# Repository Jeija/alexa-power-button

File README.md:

# Alexa / Dash Button = PC power button
If you like to hide your desktop computer case so that it's not in the way, you probably know that it can be quite annoying to have to press the power button in an uncomfortable location every time you want to turn on your PC. `alexa-power-button` solves this by enabling you to use both voice commands for Amazon's digital assistant "Alexa" and/or an Amazon Dash Button to start your computer.

## Hardware
`alexa-power-button` doesn't use Wake on LAN so that you can save energy by turning off all of the attached network equipment apart from a single WiFi router in your home. Instead, the only additional active device is a small ESP32-based PCB inside the computer case that can be programmed and powered using the mainboard's internal USB connectors. Most mainboards can charge phones and other USB devices while the PC is turned off, and this current is more than enough to power the ESP32. The PCB contains n-channel MOSFETs that can be used to pull the power / reset button data line low. This assumes that the power / reset button input of the mainboard consists of an active-low input pin with a positive bias voltage. This pin should then be connected to the MOSFET's drain.

The KiCad design files (schematic, PCB layout) are provided in `hardware`.

## Dash Button Setup
* Use the Amazon App to configure the dash button
* In the last step, don't select which of the products in the list to order
* Press the dash button and use wireshark or similar tools to get the button's MAC address
* In the `firmware` directory: Execute `idf.py menuconfig` and enter the Dash Button's MAC Address in `Alexa Power Button --> Dash Button MAC Address` (including colons)

After flashing the firmware, the ESP32 will capture all WiFi traffic and check if source or destination address of the IEEE 802.11 header match the provided Dash Button MAC address.

## Alexa Skill + AWS MQTT / Lambda Setup
* Follow some of the [commonly available](https://www.hackster.io/darian-johnson/diy-smart-lamp-controlled-by-toggle-switch-and-alexa-7de243) [tutorials](https://developer.amazon.com/blogs/post/Tx4WG410EHXIYQ/five-steps-before-developing-a-smart-home-skill) on how to create an Alexa Skill, set up a Lambda function and set up AWS IoT for MQTT
* Make sure to select Payload Version `v2 (legacy)` when creating the Alexa Skill
* Upload the Lambda function. If you have the AWS CLI set up, you can use the Makefile provided in `aws` to upload and test the code.
* Add `THING_ENDPOINT` (AWS IoT HTTPS REST API endpoint host, see the thing's Interact page in AWS IoT) and `MQTT_BASE_TOPIC` (prefix for MQTT topic, e.g. `myhome/mypc`) as environment variables for the Lambda function
* Get your device private key and device certificate from AWS IoT and copy them to `firmware/main/certs` as `private.pem.key` and `certificate.pem.crt` respectively. See [esp-idf's AWS IoT documentation](https://github.com/espressif/esp-idf/tree/master/examples/protocols/aws_iot) for details.
* Confgiure the firmware: Run `idf.py menuconfig` in `firmware` and add your WiFi SSID and password in `Alexa Power Button`. Configure your (arbitrary but unique) AWS IoT Client ID and add the same MQTT base topic as specified in your Lambda function environment variable. Under `Component Config --> Amazon Web Services IoT Platform`, add your AWS IoT HTTPS REST API endpoint host, see the thing's Interact page on AWS IoT.
* Flash the firmware. If errors occur while connecting to AWS IoT, see [the documentation in esp-idf](https://github.com/espressif/esp-idf/tree/master/examples/protocols/aws_iot) for some common problems.

## Flash the firmware
* Use `idf.py menuconfig` in `firmware` to configure your python executable, serial port and flasher baud rate
* `alexa-power-button` uses the usual esp-idf CMake build system and workflow. Run `idf.py all` and `idf.py flash` in `firmware` in order to compile and flash the firmware to your ESP32 board.

## Attribution
* ESP32 schematic symbol and footprint: [adamjvr's ESP32-kiCAD-Footprints
](https://github.com/adamjvr/ESP32-kiCAD-Footprints)
* Alexa Skill Lambda function validation (`aws/validation.js`): [Amazon's alexa-smarthome-validation](https://github.com/alexa/alexa-smarthome-validation)
* ESP32 code: Roughly based on esp-idf's [AWS IoT Subscribe/Publish Example](https://github.com/espressif/esp-idf/tree/master/examples/protocols/aws_iot/subscribe_publish)

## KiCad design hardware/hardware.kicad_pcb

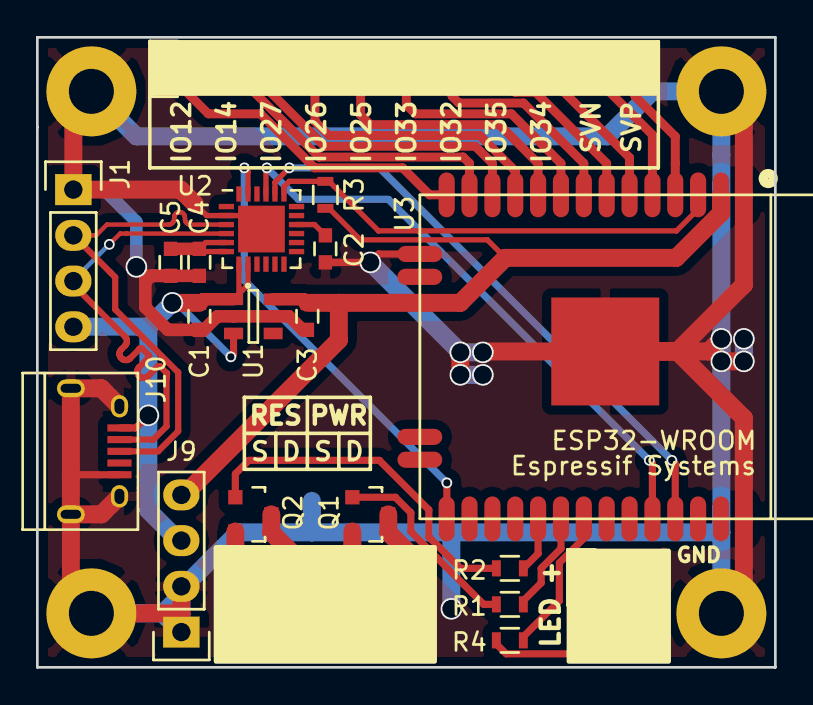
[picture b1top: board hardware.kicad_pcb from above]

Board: 2 copper layers, 41.0 x 35.0 mm, 24 parts (0 on the bottom side), 33 nets.

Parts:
C1, C3: 1u; C_0603
C2, C4: 4.7u; C_0603
C5: 100n; C_0603
J1: USB; Pin_Header_Straight_1x04
J2: PWRLED; Pin_Header_Straight_1x02
J3: GPIO; Pin_Header_Straight_1x11
J4, J7: PWRSW; Pin_Header_Straight_2x01
J5, J8: RSTSW; Pin_Header_Straight_2x01
J6: PWRLED; Pin_Header_Straight_2x01
J9: Conn_01x04; Pin_Header_Straight_1x04
J10: USB_OTG; USB_Micro-B
Q1, Q2: IRLML 6344; SOT-23
R1, R2: 1K; R_0603
R3: 12K; R_0603
R4: 10K; R_0603
U1: TLV70033; SOT-23-5
U2: CP2104; QFN-24-1EP_4x4mm_Pitch0.5mm
U3: ESP32-WROOM

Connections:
+3V3: C3.1, J9.4, R3.1, U1.5, U3.2
+5V: C1.1, J1.4, J9.3, J10.1, U1.1, U1.3, U2.7, U2.8
/ESP_EN: R3.2, U2.19, U3.3
/ESP_RXD: U2.21, U3.34
/ESP_TXD: U2.20, U3.35
/PWRLED: R4.1, U3.31
/PWRSW: R1.2, U3.30
/RSTSW: R2.2, U3.29
/USB_D+: J1.2, J10.3, U2.3
/USB_D-: J1.3, J10.2, U2.4
/~ESP_FLASH: U2.23, U3.25
GND: C1.2, C2.2, C3.2, C4.2, C5.2, J1.1, J9.1, J9.2, J10.5, J10.6, U1.2, U2.2, U2.25, U3.1, U3.15, U3.38, U3.39
unnamed: C2.1, U2.16
unnamed: C4.1, C5.1, U2.5, U2.6
unnamed: J2.1, J6.2, R4.2
unnamed: J2.2, J6.1
unnamed: J3.1, U3.14
unnamed: J3.2, U3.13
unnamed: J3.3, U3.12
unnamed: J3.4, U3.11
unnamed: J3.5, U3.10
unnamed: J3.6, U3.9
unnamed: J3.7, U3.8
unnamed: J3.8, U3.7
unnamed: J3.9, U3.6
unnamed: J3.10, U3.5
unnamed: J3.11, U3.4
unnamed: J4.1, J7.2, Q1.2
unnamed: J4.2, J7.1, Q1.3
unnamed: J5.1, J8.2, Q2.2
unnamed: J5.2, J8.1, Q2.3
unnamed: Q1.1, R1.1
unnamed: Q2.1, R2.1

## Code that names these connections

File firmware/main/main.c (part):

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
/*
 * GPIO configuration
 * RSTSW_GPIO: (Output) Pin that the gate of the reset switch n-channel MOSFET is connected to
 * PWRSW_GPIO: (Output) Pin that the gate of the power switch n-channel MOSFET is connected to
 * The positive voltage-biased power / reset switch connector of the mainboard should be connected
 * to the respective n-channel MOSFET's drain while the respective ground connector should be connected
 * to the MOSFET's source. Use a multimeter to check which of your mainboard's power / reset switch pins
 * is tied to ground and which one is the active-low input.
 * These pins are used to turn on / turn off / reset the computer.
 * PWRLED_GPIO: (Input) Pin that the power led indicator of the mainboard is connected to
 * This pin is used to get the computer's power status.
 */
#define RSTSW_GPIO 5
#define PWRSW_GPIO 18
#define PWRLED_GPIO 19

/*
 * MQTT topics to subscribe to and process
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
	uint8_t gpio = 0;
	if (strncmp(topic, MQTT_TOPIC_RST, topic_len) == 0)
		gpio = RSTSW_GPIO;
	else if (strncmp(topic, MQTT_TOPIC_PWR, topic_len) == 0)
		gpio = PWRSW_GPIO;
	else {
		ESP_LOGW(TAG, "MQTT: Unknown topic %.*s, ignoring", topic_len, topic);
		return;
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			dash_button_blocked = true;
			TimerHandle_t unblock_timer = xTimerCreate("dashUnblockTimeout", DASH_UNBLOCK_TIMEOUT / portTICK_RATE_MS, false, NULL, dashUnblockTimeout);
			xTimerStart(unblock_timer, 0);
			switchPushAndRelease(PWRSW_GPIO);
		}
	}
}
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
void app_main() {
	wifi_init();
	switchInit(PWRSW_GPIO);
	switchInit(RSTSW_GPIO);
	xTaskCreatePinnedToCore(&mqtt_task, "mqtt_task", 36 * 1024, NULL, 5, NULL, 1);
}

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
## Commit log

2017-11-02 Initial upload, supports Alexa + Dash Button
    Currently only supports turning on your computer,
    optional TODOs: Reset switch, get power status through MQTT
2018-04-07 Firmware: Updates for latest esp-idf, increase dash unblock timeout
2019-09-06 Migrate to new esp-idf and CMake-based build system, update to esp-aws-iot
2019-09-06 Update README to esp-idf's new CMake-based build system
2022-01-03 Add jsmn dependency via IDF component registry
